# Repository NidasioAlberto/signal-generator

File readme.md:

# Signal Generator with an STM32

## Introduction

The main idea of this project is to develop a waveform generator instrument using an STM32 microcontroller and its built-in DAC. The project has 2 parts:
- **Software**: The application needs to showcase the STM32 capability to output
            waveforms  at sample rates of 100kHz or greater. The software has to include a
            peripheral driver to access the built in DAC using DMA.
- **Hardware**: The device has to to implement a waveform generator output stage
            circuitry that allows to extend the capabilities of the built in DAC.

To achieve this goals a custom board was designed and software drivers were developed for the DAC and DMA. The final product also includes a text interface where the user can setup an arbitrary waveform and the device parses the user input using Flex and Bison.

<div align="center">

</div>

## Analog Front End

The stm32 incorporates a Digital-to-Analog Converter (DAC) with an integrated output buffer. When enabled, the buffer allows the DAC to drive external loads directly. However, this comes at the cost of limited driving capability, especially when interfacing with capacitive loads. Disabling the buffer offers a pure analog output, but necessitates an external buffer or amplifier to drive any meaningful external load. The inherent impedance of the DAC's output pin can also cause distortions and constrain the signal's frequency, particularly when dealing with capacitive loads.

Integrating an external operational amplifier (op-amp) into the analog front-end offers multiple advantages:

- **Buffering DAC Output**: The op-amp serves as a buffer, isolating the DAC from the actual load. This setup minimizes the effects of the DAC output pin's impedance, enabling the DAC to operate in a near-ideal environment.
- **Voltage Scaling**: Configured in a non-inverting amplifier mode, the op-amp provides adjustable gain, facilitating flexible signal amplitude adjustments.

Given that the board is powered via USB, which typically provides 5V, there's a need to step up this voltage to achieve the 12V requirement for the analog front end:

- **Boost Converter**: The TLV61048 boost converter is employed to step up the USB's 5V to 13.12V.
- **Linear Voltage Regulator**: Following the boost converter, an LDO is used to convert the 13.12V from the boost converter to a stable 12V output. This stable 12V supply is crucial to ensure that the analog front-end, especially the operational amplifier, operates with consistency.

The opamp circuit also features a voltage divider to feedback the output signal to the STM32's ADC. This could allow the microcontroller to perform automatic calibration of the opamp gains.
Here's the provided LaTeX content converted into markdown:

## Microcontroller and digital domain

The STM32F205 is a low-end microcontroller with a 120MHz clock speed, 128KB of RAM, and the required peripherals needed by the project (DAC, DMA, and timers). It was used mainly because it was already stocked in the lab.

The board also features:
- An external 25MHz crystal oscillator to drive the microcontroller.
- A USB to UART bridge to allow the user to interact with the device via a serial terminal.
- An RGBW addressable led used for status indication.
- A header connector that exposes the SWD programming interface.
- Two buttons: one for reset and one for the BOOT0 pin.
- A microSD card slot to store files.

## Software architecture

The software powering the signal generator board is built upon the [Miosix operating system](https://github.com/NidasioAlberto/miosix-kernel) and features 2 main components:
- Drivers for the DAC and DMA peripherals.
- A parser built using Flex and Bison that allows interpreting the user input into arbitrary math functions used to generate the output waveform.

### Peripherals drivers

The STM32F205 microcontroller is equipped with a versatile Digital-to-Analog Converter (DAC) peripheral that offers 12-bit resolution and two separate channels, effectively incorporating two DACs. This dual-channel architecture permits simultaneous generation of two distinct analog outputs, allowing our custom board to feature two independent output channels.

The DAC's conversion process can be initiated through multiple methods. It can be triggered manually via software, which provides direct control over the conversion timing. Alternatively, for applications requiring precise and periodic analog outputs, external triggers can be employed. A common external trigger source is a timer, which can initiate DAC conversions at predetermined intervals, ensuring consistent waveform generation.

The STM32's DAC is also designed with the capability to generate DMA requests. Once the DAC is ready for new data, it can signal the DMA peripheral to fetch the next data sample. The DMA (Direct Memory Access) controller is a powerful tool designed to handle data transfers independently of the CPU's operation. This peripheral is characterized by sixteen independent streams, each of which can be paired with different peripherals, granting a wide range of configuration possibilities. By leveraging the DMA's rapid data transfer capabilities, the DAC can be persistently supplied with data while leaving the CPU time to generate new data samples or perform other tasks.

One of its standout features is the double buffering mode. This mode uses two memory pointers: while one buffer is actively engaged by the DMA stream, the other can be prepared by the CPU, ensuring uninterrupted data flow.

In the context of the signal generator project, the DMA plays a crucial role. Each DAC is set up to utilize an external trigger originating from a timer. With every trigger event, the DAC issues a DMA request for a new data sample. The DMA has been configured in double buffer mode. Alternatively, a single buffer mode combined with the half-transfer interrupt could have been adopted to achieve a similar result. This integration of the DAC with the DMA and a timer is what ultimately powers the project's ability to generate high-frequency waveforms even with a low-end microcontroller such as the STM32F205.

The developed drivers are C++ classes that abstract the peripherals and allow the programmer to easily configure and use them. In particular, the DMA driver is divided into two classes and one struct:
- **DMADriver**: A singleton that manages all DMA streams. When a piece of code needs a stream, it can request it to the DMADriver. If the stream is already in use, the DMADriver will pause the thread until the stream is available, otherwise, it will acquire the stream and return it to the caller.
- **DMATransaction**: A struct that holds all configuration parameters for a specific transfer. This includes source and destination addresses, data size, double buffer, interrupts, and so on.
- **DMAStream**: This class allows configuring the stream for a specific transaction, start and stop it, and easily handle interrupts. In particular, interrupts can be waited for with or without a timeout (thanks to the Miosix's timed wait feature) or registering a callback function that will be called when the interrupt occurs.

# Project outcomes

## Concrete outcomes

The project achieved two concrete outcomes:
- **Electronic board**: The board was designed and assembled successfully. It includes an analog front end that extends the capabilities of the STM32's built-in DAC and also includes features, such as the ADC feedback and micro SD, that allows further experimentation.
- **Software drivers**: Two software drivers were developed, one for the DAC and one for the DMA. These allow the use of the peripherals in a simple and efficient way.

## Learning outcomes

Developing both the hardware and the software allowed me not only to learn about the STM32 microcontroller and its peripherals but also to learn about the whole process of designing and assembling a PCB.

Particular effort went into the design of the board itself, selecting and sourcing the components, and manually assembling the board. It was a challenge because, being my first time creating a complex PCB with a microcontroller, I was not well prepared. I had to learn about the different types of components, which were required for my design, and which not. Some special takeaways were the importance of reading carefully the components datasheet, finding application notes to understand similar projects, and learning how to design and order a PCB (with KiCad and JLCPCB).

The assembly of the board was the most exciting part because I got to see my design come to life. I procured the necessary soldering equipment (solder paste, a hot plate, a hot air gun, and a microscope) and I soldered the board first by distributing the solder paste with a stencil and then by heating the board with the hot plate for the top layer, and with the hot air gun for the bottom layer. I had to learn how to use the equipment and how to solder the different components.

The software side was instead more akin to my previous experiences. I had already worked with microcontrollers and already used the Miosix operating system. However, I had never worked with the DMA peripheral. The most challenging aspects were understanding how the peripherals work by reading the reference manual and also finding examples online which are hard to come by.

## Existing knowledge

The most useful knowledge that helped me in this project came from 3 sources:
- **Advanced Operating System**: In particular, the parts on concurrency, thread programming, and analysis of the features in the Miosix operating system.
- **Embedded Systems**: The course gave me a good understanding of the development process of a microcontroller-based system, both for the design aspects and for the production processes involved.
- **Skyward Experimental Rocketry**: Most of the experience I had prior to this academic year was my involvement in the Skyward Experimental Rocketry team. Previously I was involved in the design and development of the software for the rocket. This year I also had the responsibility of managing the production of the avionic system as a whole, including the electronic part. This gave me a good opportunity to work on another project and the luck of knowing lots of talented teammates.

## Problems encountered

The worst setback I faced was the board redesign. In the first version, I used an STM32F103 which is a cheaper microcontroller that has no built-in DAC! I realized this only after I had assembled the board and tried to use it. I had to adjust the schematic and the PCB in order to use the STM32F205 instead and reorder the board.

Once the board was ready I faced other problems during the development of the drivers but I managed to solve them without major issues. In this process, the debugger was particularly useful to understand what was going on.

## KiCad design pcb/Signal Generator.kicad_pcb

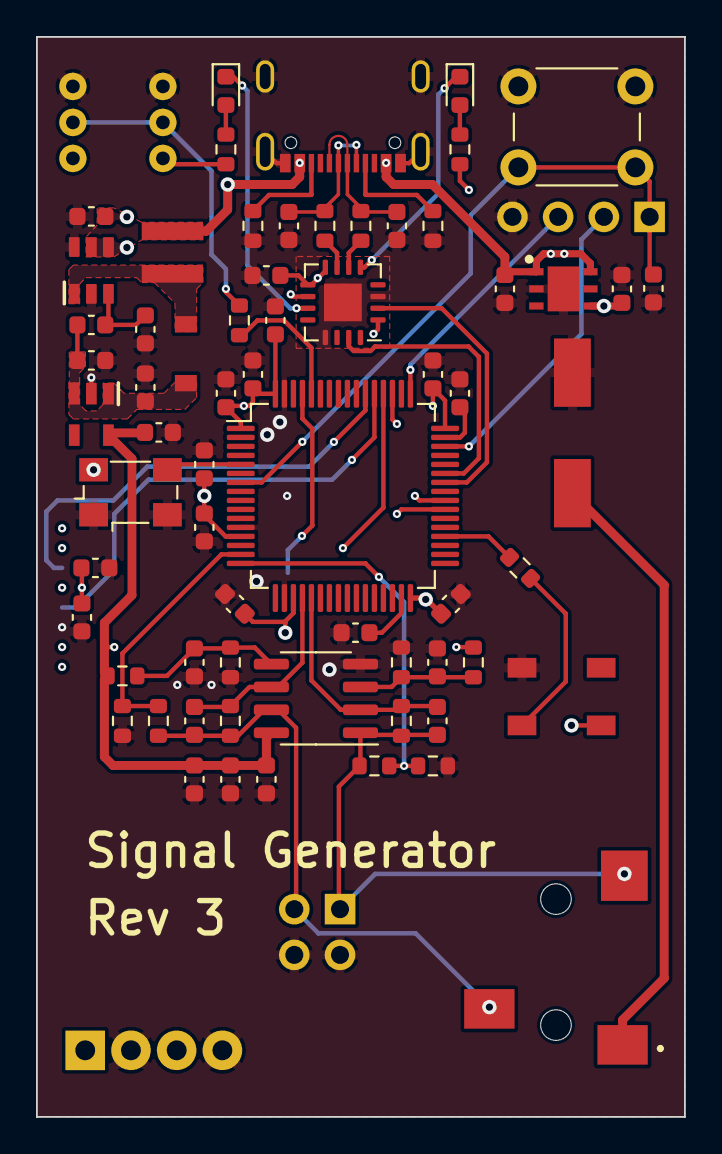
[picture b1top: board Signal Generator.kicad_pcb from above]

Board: 4 copper layers, 36.0 x 60.0 mm, 70 parts (1 on the bottom side), 46 nets.

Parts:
C1, C28: 10u; C_0603_1608Metric
C2: 330u; WCAP-PSHP
C3, C6, C7, C8, C12, C16, C17, C18, C19, C20, C21, C23: 100n; C_0603_1608Metric
C4, C5: 47p; C_0603_1608Metric
C9, C10: 0.5p; C_0603_1608Metric
C11: 100p; C_0603_1608Metric
C13: 6.8u; C_0603_1608Metric
C14, C15: 2.2u; C_0603_1608Metric
C22, C25, C26, C27, C29, C30: 1u; C_0603_1608Metric
C24: 4.7u; C_0603_1608Metric
D1: LED Blue; LED_0603_1608Metric
D2: LED Orange; LED_0603_1608Metric
D3: IN-PI55QA
D4: D_Zener; BZT52C10-TP
J1: AudioJack3; SJ-3523-SMT-TR
J2: Conn_02x02_Odd_Even; PinHeader_2x02_P2.54mm_Horizontal
J3: Screw_Terminal_01x04; TerminalBlock_Phoenix_MPT-0,5-4-2.54_1x04_P2.54mm_Horizontal
J4: MEM2080-00-128-00-A
J5: USB_C_Receptacle_USB2.0; USB4105-GF-A
J6: Conn_01x04; PinHeader_1x04_P2.54mm_Vertical
L1: 4.7u; XAL4030
R1, R2: 27; R_0603_1608Metric
R3, R4: 5.1k; R_0603_1608Metric
R5: 3.32; R_0603_1608Metric
R6: 43.2; R_0603_1608Metric
R7, R9: 4.75k; R_0603_1608Metric
R8, R10: 1.33k; R_0603_1608Metric
R11, R12: 46.4k; R_0603_1608Metric
R13, R15: 240k; R_0603_1608Metric
R14, R16: 91k; R_0603_1608Metric
R17: 1k; R_0603_1608Metric
R18: 10k; R_0603_1608Metric
R19: 1.54M; C_0603_1608Metric
R20: 100k; C_0603_1608Metric
SW1: SW_Push; SW_PUSH_6mm_H5mm
SW2: SW_SPDT; Push Button Switch 7x7mm
U1: FT230XQ; QFN-16-1EP_4x4mm_P0.65mm_EP2.1x2.1mm
U2: Opamp_Dual; SOIC-8_3.9x4.9mm_P1.27mm
U3: STM32F205RCTx; LQFP-64_10x10mm_P0.5mm
U4: FT5HN; Oscillator_SMD_Fox_FT5H_5.0x3.2mm
U5: LD39050PU33R
U6: TLV61048
U7: LDK320AM120R

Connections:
+3.3V: C1.1, C3.1, C16.1, C17.1, C18.1, C19.1, C20.1, C21.1, C22.1, C24.1, C27.1, J4.P4 (VDD), R5.1, R6.2, SW2.3 (C), U3.1 (VBAT), U3.13 (VDDA), U3.19 (VDD), U3.32 (VDD), U3.48 (VDD), U3.64 (VDD), U4.4 (VDD), U5.4 (VOUT)
+5V: C25.1, C26.1, D3.3 (VDD), J5.A4 (VBUS), J5.A9 (VBUS), J5.B4 (VBUS), J5.B9 (VBUS), L1.1, U1.10 (VCC), U5.1 (EN), U5.6 (VIN), U6.4 (EN), U6.5 (VIN)
+12VA: C11.1, C12.1, C13.1, C30.1, R7.2, R9.2, U2.8 (V+), U7.5 (OUT)
/ADC1: R15.2, R16.1, U3.15 (PA1)
/ADC2: R13.2, R14.1, U3.16 (PA2)
/DAC1: C10.1, R12.1, U2.6 (-), U3.20 (PA4)
/DAC2: C9.1, R11.1, U2.2 (-), U3.21 (PA5)
/MCU/BOOT0: R18.1, U3.60 (BOOT0)
/MCU/LED_DIN: R17.1, U3.36 (PB15)
/MCU/NRST: C23.1, J6.1, SW1.2, U3.7 (NRST)
/MCU/OSC: U3.5 (PH0), U4.3 (OUT)
/MCU/SWCLK: J6.3, U3.49 (PA14)
/MCU/SWDIO: J6.2, U3.46 (PA13)
/MCU/UART1_RX: U1.15 (TXD), U3.43 (PA10)
/MCU/UART1_TX: U1.2 (RXD), U3.42 (PA9)
/Output Stage/CH1_OUT: C10.2, J1.R, J2.3, J3.1, R12.2, R15.1, U2.7
/Output Stage/CH2_OUT: C9.2, J1.T, J2.1, J3.3, R11.2, R13.1, U2.1
/Power/13.12V: C28.1, C29.1, D4.1 (K), R19.1, U7.1 (IN), U7.3 (EN)
/SD_CMD: J4.P3 (CMD), U3.54 (PD2)
/SD_D0: J4.P7 (DAT0), U3.39 (PC8)
/SD_D1: J4.P8 (DAT1), U3.40 (PC9)
/SD_D2: J4.P1 (DAT2), U3.51 (PC10)
/SD_D3: J4.P2 (CD/DAT3), U3.52 (PC11)
/SD_Detect: J4.DSW2 (Switch), U3.61 (PB8)
/SD_SCK: J4.P5 (CLK), U3.53 (PC12)
/USB Connector/CC1: J5.A5 (CC1), R4.2
/USB Connector/CC2: J5.B5 (CC2), R3.1
/USB Connector/FT_3V3: C6.1, U1.1 (VCCIO), U1.8 (3V3OUT), U1.9 (~RESET)
/USB Connector/USB_D+: C4.1, J5.A6 (D+), J5.B6 (D+), R2.2
/USB Connector/USB_D-: C5.1, J5.A7 (D-), J5.B7 (D-), R1.1
GND: C1.2, C2.2, C3.2, C4.2, C5.2, C6.2, C7.2, C8.2, C11.2, C12.2, C13.2, C14.2, C15.2, C16.2, C17.2, C18.2, C19.2, C20.2, C21.2, C22.2, C23.2, C24.2, C25.2, C26.2, C27.2, C28.2, C29.2, C30.2, D3.1 (VSS), J2.2, J2.4, J3.2, J3.4, J4.DSW1 (Lever), J4.P6 (VSS), J5.A1 (GND), J5.A12 (GND), J5.B1 (GND), J5.B12 (GND), J5.S1 (SHIELD), J6.4, R3.2, R4.1, R8.1, R10.1, R14.2, R16.2, R20.2, SW1.1, SW2.1 (A), U1.3 (GND), U1.13 (GND), U1.17 (GND), U2.4 (V-), U3.12 (VSSA), U3.18 (VSS), U3.63 (VSS), U4.1 (GND), U4.2 (GND), U5.2 (GND), U5.7 (PAD), U6.2 (GND), U6.6 (FREQ), U7.2 (GND)
unnamed: C2.1, J1.S
unnamed: D1.2 (A), R5.2
unnamed: D1.1 (K), U1.11 (CBUS1)
unnamed: D2.2 (A), R6.1
unnamed: D2.1 (K), U1.5 (CBUS2)
unnamed: D3.2 (DIN), R17.2
unnamed: D4.2 (A), L1.2, U6.1 (SW)
unnamed: R18.2, SW2.2 (B)
unnamed: R1.2, U1.7 (USBDM)
unnamed: R2.1, U1.6 (USBDP)
unnamed: C7.1, R7.1, R8.2, U2.3 (+)
unnamed: C8.1, R9.1, R10.2, U2.5 (+)
unnamed: C14.1, U3.31 (VCAP_1)
unnamed: C15.1, U3.47 (VCAP_2)
unnamed: R19.2, R20.1, U6.3 (FB)

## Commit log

2022-10-28 [miosix] Added miosix-kernel submodule
2022-10-28 [report] Added latex template
2022-10-28 Added .gitignore file
2022-10-28 Added basic configuration
2022-10-28 Updated dac test entrypoint
2022-10-31 Tested DAC wave generator
2022-10-31 Added documents
2022-10-31 Prepared the LaTeX document
2022-11-08 Updated documentation docs
2022-11-08 Updated miosix-kernel
2022-11-08 Tested DAC with DMA and timer
2022-11-09 Added application note document
2022-11-14 Updated VSCode debug launch configuration
2022-11-14 Tested DAC and DMA with new drivers
2022-11-23 Tested the new DMA driver
2022-11-25 First attempt at adding support for the stm32f769ni discovery
2022-11-25 Added some useful documents
2022-12-19 Added new documents
2022-12-19 Created basic KiCad project with an stm32f103
2023-01-09 Updated report
2023-01-09 Updated documents
2023-01-09 Updated pcb
2023-01-11 Updated schematic with almost final front end
2023-01-12 Updated pcb library
2023-01-12 Added connectors and organized schematic in multiple sheets
2023-01-13 Completed schematic oranization and components connection
2023-01-15 Added micro SD and RGB led to schematic. Also added components part numbers
2023-01-16 Completed schematic and tried some simulations
2023-01-16 Added ST-Link connector to schematic
2023-01-16 Added blocking capacitor to headphones jack
2023-01-16 Updated some footprints
2023-01-28 Completed PCB and prepared production files
2023-02-28 Updated PCB to correct some connection errors
2023-04-11 Fixed FTDI connection to the stm32
2023-04-11 Added new build system
2023-04-11 Configured c_cpp_properties
2023-04-18 Switch to stm32f205
2023-05-05 Prepared PCB rev 3
2023-05-05 Ported SPI driver from Boardcore
2023-05-05 Ported timer drivers from Boardcore
2023-05-05 Added DMA driver
2023-05-05 Added DAC driver
2023-05-05 Added test entrypoints
2023-05-19 Added support for custom target stm32f205rc_signal_generator
2023-05-23 Added ADC driver
2023-05-23 Fixed DAC buffer
2023-05-28 Created basic entrypoint with Flex and Bison
2023-05-28 Prepared demo of function parser
2023-06-19 Tested DMA double buffering to generate a continuous wave
2023-06-19 Updated parser with start and stop commands
2023-06-19 Tested SPI with DMA and RGB led
2023-06-20 Added interrupts flags management to DMA driver
2023-06-21 Updated kernel to latest commit on testing
2023-06-21 Added interrupt handling to DMA driver
2023-06-21 Updated dac with dma test
2023-06-24 Updated footprint of IN-PI55QA led
2023-06-24 Moved pcb files in pcb folder
2023-06-24 Fixed timers trigger sources for stm32f205
2023-06-24 Updated CMakeLists to use homebrew Bison path on MacOS
2023-06-24 Updated parser and created main application entrypoint
2023-06-24 Added Color struct to RGB led
2023-06-26 Moved all code into code folder
2023-06-26 Fixed copyright notice
2023-07-07 Updated pbc library paths
2023-08-14 Updated ClockUtils and TimerUtils with support for f7 micros
2023-08-14 Updated ADC driver with support for regular sequence trigger
2023-08-14 Added HUE clor type to the RGB led
2023-08-14 Added help message and improved user interface
2023-08-15 Divided Generator class into .h and .cpp files
2023-08-15 Added CPU command to print CPU usage
2023-08-15 Change some paths
2023-08-15 Fixed compilation issues with CMake
2023-08-17 Added Fixed-Point Math library
2023-08-17 Implemented fixed point library
2023-08-20 Prepared report and readme page
2023-08-21 Updated report makefile
2023-08-22 Fixed DMA driver and added getCurrentBufferNumber function
2023-08-22 Renamed function timedWaitFlag into timedPollingFlag
2023-08-30 Updated ChannelCtrlData struct and moved wave generation into threads
2023-08-30 Fixed compilation
2023-08-30 Added error callback and updated flags handling
    Now the flags status is saved and can be accessed later
2023-08-30 Added checks for multiple starts and stops and fixed channel 1 thread
2023-08-30 Prepared basic example for generating a wave with DAC, DMA and timer
